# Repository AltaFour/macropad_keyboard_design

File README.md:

# macropad_keyboard_design
Software Used:
Autodesk Fusion 360 (Cad Software that is free for personal projects)
KiCad (Open Source PCB design software)
Github
Git

Manufacturing:
JLCPCB

This is the manufactured board without the components on it. I took this, solder paste and a aluminuim stencil and assembled the components on the board. I then put it in our toaster over and turned it up to full heat until all of the paste turned silver and metalic meaning that the connection was bridged.

This is a screenshot of the PCB design from KiCad which is a free open source pcb design software. I formatted this and sent it off to JLC PCB and they sent me the boards which are shown above.

This is a picture of the final product. I used SMD soldering to attach all the components. It has been flashed with QMK and works perfectly. I also designed a case that I am going to have 3d printed once we finish building our 3d printer(will attach pictures with case after).

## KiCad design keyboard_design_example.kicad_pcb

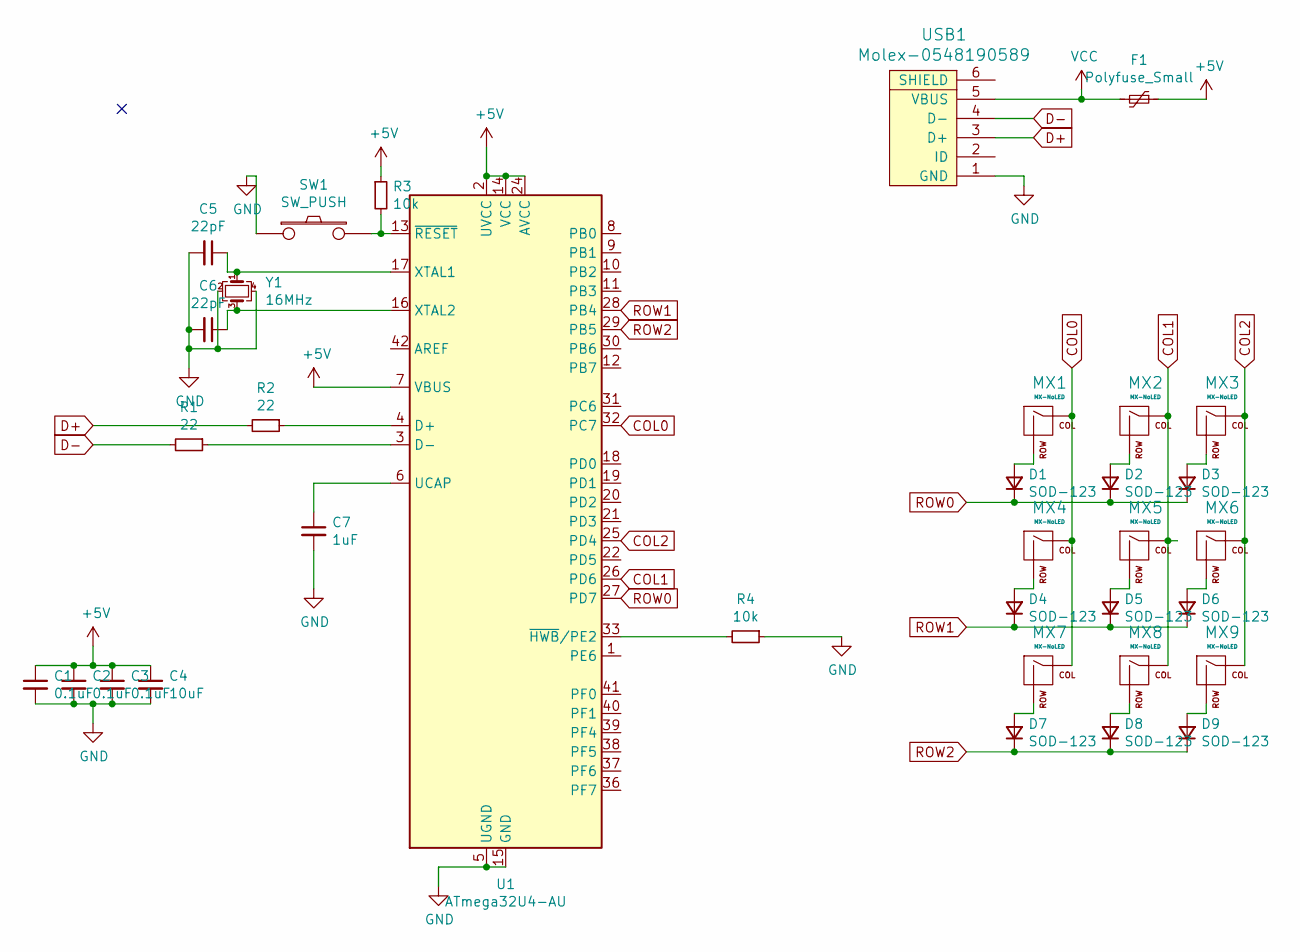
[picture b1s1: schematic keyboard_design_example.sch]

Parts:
C1, C2, C3: 0.1uF; C_0805_2012Metric
C4: 10uF; C_0805_2012Metric
C5, C6: 22pF; C_0805_2012Metric
C7: 1uF; C_0805_2012Metric
D1, D2, D3, D4, D5, D6, D7, D8, D9: SOD-123; D_SOD-123
F1: Polyfuse_Small; Fuse_1206_3216Metric
MX1, MX2, MX3, MX4, MX5, MX6, MX7, MX8, MX9: MX-NoLED; MXOnly-1U-NoLED
R1, R2: 22; R_0805_2012Metric
R3, R4: 10k; R_0805_2012Metric
SW1: SW_PUSH; SKQG-1155865
U1: ATmega32U4-AU; TQFP-44_10x10mm_P0.8mm
USB1: Molex-0548190589
Y1: 16MHz; Crystal_SMD_3225-4Pin_3.2x2.5mm

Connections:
+5V: C1.1, C2.1, C3.1, C4.1, F1.1, R3.1, U1.2 (UVCC), U1.7 (VBUS), U1.14 (VCC), U1.24 (AVCC), U1.34 (VCC), U1.44 (AVCC)
COL0: MX1.1 (COL), MX4.1 (COL), MX7.1 (COL), U1.32 (PC7)
COL1: MX2.1 (COL), MX5.1 (COL), MX8.1 (COL), U1.26 (PD6)
COL2: MX3.1 (COL), MX6.1 (COL), MX9.1 (COL), U1.25 (PD4)
D+: R2.2, USB1.3 (D+)
D-: R1.2, USB1.4 (D-)
GND: C1.2, C2.2, C3.2, C4.2, C5.2, C6.2, C7.2, R4.1, SW1.1, U1.5 (UGND), U1.15 (GND), U1.23 (GND), U1.35 (GND), U1.43 (GND), USB1.1 (GND), Y1.2, Y1.4
unnamed: C5.1, U1.17 (XTAL1), Y1.1
unnamed: C6.1, U1.16 (XTAL2), Y1.3
unnamed: C7.1, U1.6 (UCAP)
unnamed: D1.2 (A), MX1.2 (ROW)
unnamed: D2.2 (A), MX2.2 (ROW)
unnamed: D3.2 (A), MX3.2 (ROW)
unnamed: D4.2 (A), MX4.2 (ROW)
unnamed: D5.2 (A), MX5.2 (ROW)
unnamed: D6.2 (A), MX6.2 (ROW)
unnamed: D7.2 (A), MX7.2 (ROW)
unnamed: D8.2 (A), MX8.2 (ROW)
unnamed: D9.2 (A), MX9.2 (ROW)
unnamed: R1.1, U1.3 (D-)
unnamed: R2.1, U1.4 (D+)
unnamed: R3.2, SW1.2, U1.13 (~RESET)
unnamed: R4.2, U1.33 (~HWB~/PE2)
ROW0: D1.1 (K), D2.1 (K), D3.1 (K), U1.27 (PD7)
ROW1: D4.1 (K), D5.1 (K), D6.1 (K), U1.28 (PB4)
ROW2: D7.1 (K), D8.1 (K), D9.1 (K), U1.29 (PB5)
VCC: F1.2, USB1.5 (VBUS)

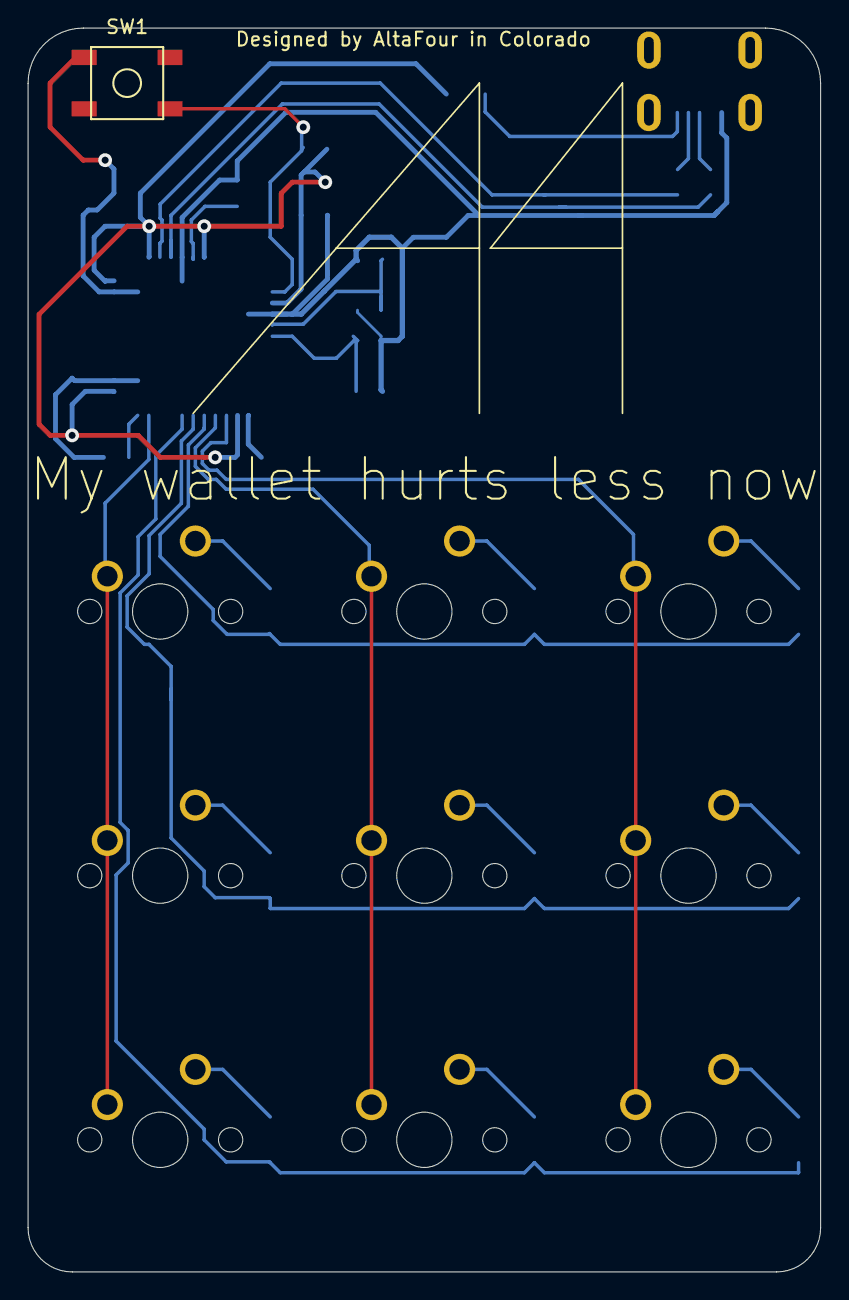
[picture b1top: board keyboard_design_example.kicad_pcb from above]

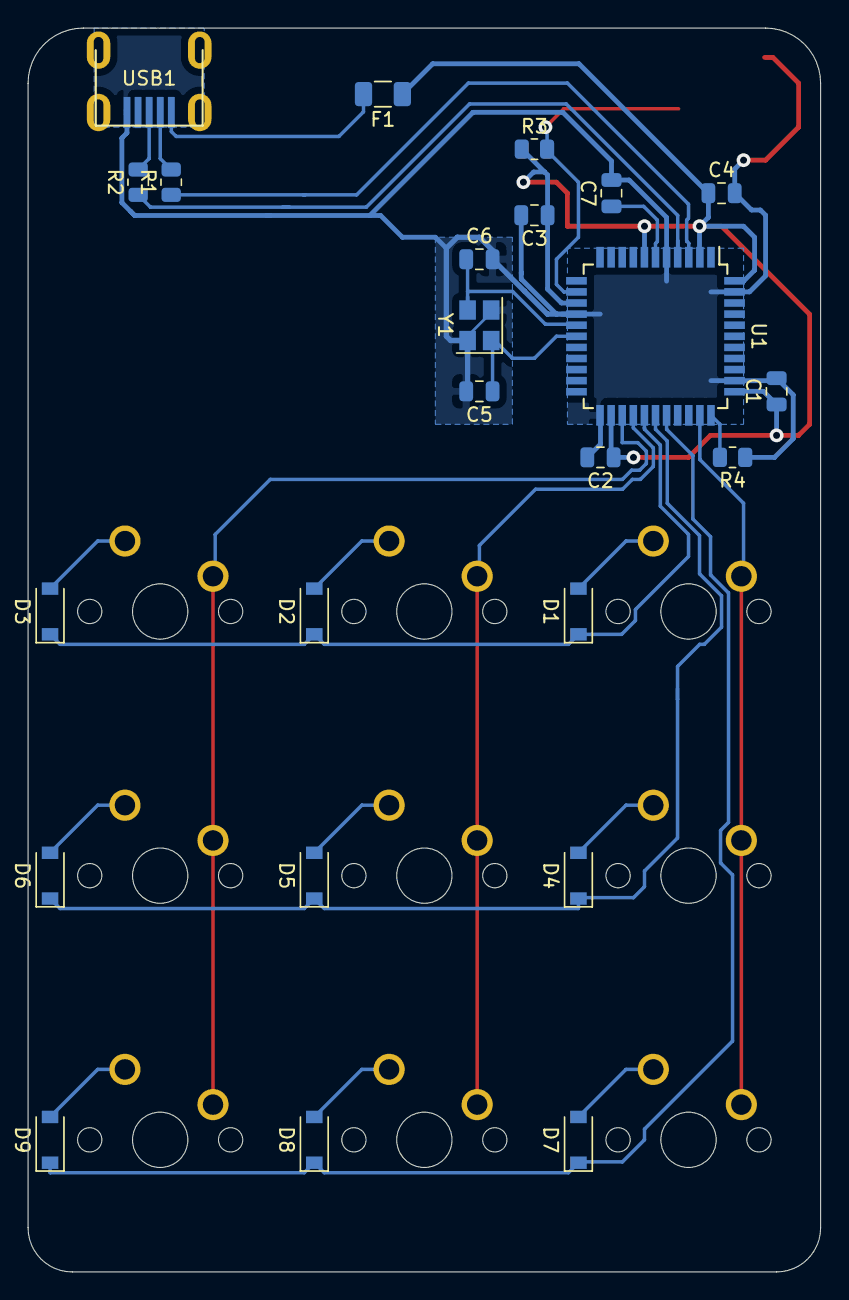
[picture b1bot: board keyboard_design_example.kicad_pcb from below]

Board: 2 copper layers, 57.1 x 89.7 mm, 34 parts (24 on the bottom side), 27 nets.

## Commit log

2021-02-07 Test
    we gotta test
2021-02-07 test 2
2021-02-07 Created Files
    Created initial files for the project.
2021-02-07 Add submodules
2021-02-08 Added Footprint Libraries
    For fooprints such a switches and stuff when doing pcb.
2021-02-08 Create _autosave-keyboard_design_example.sch
    updated autosave
2021-02-08 Updating
    Finished Schematic, moving onto pcb
2021-02-08 Update
    Started PCB Design
2021-02-10 Update and work
2021-02-15 2x2 bad 3x3 good
    Updated schematic for a 3x3 mx switch cluster.
2021-02-15 Update
    Working on pcb organization
2021-02-15 Update
    stuff
2021-02-16 Update
    Did the crystal tracing POGGERS
2021-02-16 Update
    Did Stuff
2021-02-16 Finished
    WOOOO I think i finished. Might have to do some updates for fixes but its going good.
2021-02-16 Finished
    Did Some Edits. Its done. Seeking feedback
2021-02-16 Vertical MCU/usb
    Made the usb and MCU face vertically and rewired the switch matrix to the mcu
2021-02-16 Finishing touches
    yes
2021-02-17 Update
    Still messing with it
2021-02-17 Resources
    Included resources that i am using for this project.
2021-02-22 Finished!!!
    I finally finished the pcb. It looks great and has my logo on it. Im gonna start my alice board project and try to get this one manufactured.
2021-04-12 Firmware/Finish
    Created working firmware that works well and I have officially finished the project.
2021-04-26 Images
2021-04-26 test
2021-04-26 Image Update
